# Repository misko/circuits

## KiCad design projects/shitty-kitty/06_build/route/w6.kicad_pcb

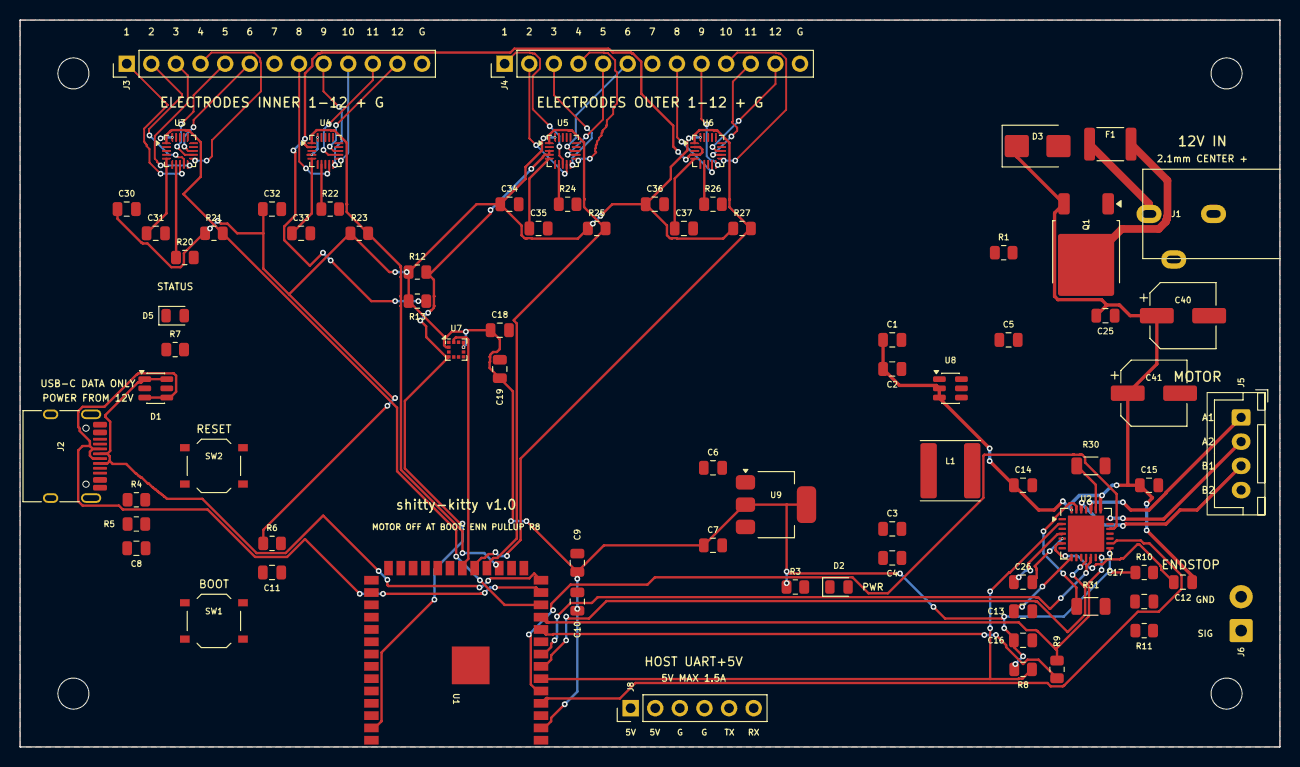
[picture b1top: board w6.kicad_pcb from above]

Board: 4 copper layers, 130.0 x 75.0 mm, 82 parts (0 on the bottom side), 79 nets.

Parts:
C1, C2: 4.7u buck in; C_0805_2012Metric
C3, C4: 22u buck out; C_0805_2012Metric
C5: 100n BST; C_0805_2012Metric
C6: 4.7u LDO in; C_0805_2012Metric
C7: 22u LDO out; C_0805_2012Metric
C8: 100n VBUS; C_0805_2012Metric
C9: 22u MCU 3V3; C_0805_2012Metric
C10: 100n MCU 3V3; C_0805_2012Metric
C11: 1u EN; C_0805_2012Metric
C12: 100n VCP; C_0805_2012Metric
C13: 4.7u 5VOUT; C_0805_2012Metric
C14, C15: 100n VS; C_0805_2012Metric
C16: 100n VCC_IO; C_0805_2012Metric
C17: 100n endstop; C_0805_2012Metric
C18: 100n accel; C_0805_2012Metric
C19: 22u accel; C_0805_2012Metric
C25: 100n 12V; C_0805_2012Metric
C26: 22n CP fly; C_0805_2012Metric
C30, C32, C34, C36: 100n MPR VDD; C_0805_2012Metric
C31, C33, C35, C37: 100n VREG; C_0805_2012Metric
C40: 100u 12V bulk; CP_Elec_6.3x7.7
C41: 100u VS bulk; CP_Elec_6.3x7.7
D1: USBLC6-2SC6; SOT-23-6
D2: green PWR; LED_0805_2012Metric
D3: SMBJ16A; D_SMB
D5: green STATUS; LED_0805_2012Metric
F1: 2A polyfuse 16V; Fuse_1812_4532Metric
H1, H2, H3, H4: MountingHole_3.2mm_M3
J1: DC-005C-20A 12V; DCJack_DC005_Horizontal
J2: TYPE-C-31-M-12; USB_C_Receptacle_HRO_TYPE-C-31-M-12
J3: ELECTRODES INNER; PinHeader_1x13_P2.54mm_Vertical
J4: ELECTRODES OUTER; PinHeader_1x13_P2.54mm_Vertical
J5: MOTOR NEMA17; JST_XH_B4B-XH-A_1x04_P2.50mm_Vertical
J6: ENDSTOP TERM; TerminalBlock_3.5-2P_NoSilk
J8: HOST 1x6; PinHeader_1x06_P2.54mm_Vertical
L1: 10uH SWPA6045S; L_Sunlord_SWPA6045S
Q1: AOD4185 revpol; TO-252-2
R1: 100k gate pd; R_0805_2012Metric
R3: 1k LED; R_0805_2012Metric
R4: 5.1k CC1; R_0805_2012Metric
R5: 5.1k CC2; R_0805_2012Metric
R6: 10k EN; R_0805_2012Metric
R7: 1k status LED; R_0805_2012Metric
R8: 10k ENN pu; R_0805_2012Metric
R9: 1k TMC UART; R_0805_2012Metric
R10: 10k endstop pu; R_0805_2012Metric
R11: 1k endstop ser; R_0805_2012Metric
R12: 4.7k SDA pu; R_0805_2012Metric
R13: 4.7k SCL pu; R_0805_2012Metric
R20, R22, R24, R26: 75k REXT; R_0805_2012Metric
R21, R23, R25, R27: 10k IRQ pu; R_0805_2012Metric
R30: 0.15R sense A; R_1206_3216Metric
R31: 0.15R sense B; R_1206_3216Metric
SW1: TS-1187A BOOT; SW_Push_1P1T_XKB_TS-1187A
SW2: TS-1187A RESET; SW_Push_1P1T_XKB_TS-1187A
U1: ESP32-S3-WROOM-1-N8R2; ESP32-S3-WROOM-1
U2: TMC2209-LA-T; QFN-28-1EP_5x5mm_P0.5mm_EP3.75x3.75mm
U3: MPR121QR2 0x5A; UQFN-20_3x3mm_P0.4mm
U4: MPR121QR2 0x5B; UQFN-20_3x3mm_P0.4mm
U5: MPR121QR2 0x5C; UQFN-20_3x3mm_P0.4mm
U6: MPR121QR2 0x5D; UQFN-20_3x3mm_P0.4mm
U7: LIS2DH12TR; LGA-12_2x2mm_P0.5mm
U8: AP63205WU-7; TSOT-23-6
U9: AMS1117-3.3; SOT-223-3_TabPin2

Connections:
3V3: C7.1, C9.1, C10.1, C16.1, C18.1, C19.1, C30.1, C32.1, C34.1, C36.1, R3.1, R6.1, R8.1, R10.1, R12.1, R13.1, R21.1, R23.1, R25.1, R27.1, U1.2, U2.15, U3.20, U4.4, U4.20, U5.20, U6.20, U7.2, U7.9, U7.10, U9.2
5V: C3.1, C4.1, C6.1, J8.1, J8.2, L1.2, U8.1, U9.3
ACC_INT: U1.20, U7.12
BOOT: SW1.1, U1.27
BRA: R30.1, U2.23
BRB: R31.1, U2.27
BST: C5.1, U8.6
CC1: J2.A5, R4.1
CC2: J2.B5, R5.1
CPI: C26.2, U2.5
CPO: C26.1, U2.4
DIAG: U1.7, U2.11
DIR: U1.5, U2.19
EN: C11.1, R6.2, SW2.1, U1.3
ENDSTOP_G: R11.2, U1.9
ENDSTOP_N: C17.1, J6.1, R10.2, R11.1
ENN: R8.2, U1.6, U2.2
GATE_Q1: Q1.1, R1.1
GND: C1.2, C2.2, C3.2, C4.2, C6.2, C7.2, C8.2, C9.2, C10.2, C11.2, C13.2, C14.2, C15.2, C16.2, C17.2, C18.2, C19.2, C25.2, C30.2, C31.2, C32.2, C33.2, C34.2, C35.2, C36.2, C37.2, C40.2, C41.2, D1.2, D2.1, D3.2, D5.1, J1.2, J1.3, J2.A1, J2.A12, J2.B1, J2.B12, J2.SH, J3.13, J4.13, J6.2, J8.3, J8.4, R1.2, R4.2, R5.2, R20.2, R22.2, R24.2, R26.2, R30.2, R31.2, SW1.2, SW2.2, U1.1, U1.40, U1.41, U2.3, U2.7, U2.9, U2.10, U2.13, U2.18, U2.29, U3.4, U3.6, U4.6, U5.6, U6.6, U7.3, U7.5, U7.6, U7.7, U7.8, U8.4, U9.1
HOST_RX: J8.6, U1.36
HOST_TX: J8.5, U1.37
INDEX: U1.8, U2.12
INNER1: J3.1, U3.8
INNER2: J3.2, U3.9
INNER3: J3.3, U3.10
INNER4: J3.4, U3.11
INNER5: J3.5, U3.12
INNER6: J3.6, U3.13
INNER7: J3.7, U4.8
INNER8: J3.8, U4.9
INNER9: J3.9, U4.10
INNER10: J3.10, U4.11
INNER11: J3.11, U4.12
INNER12: J3.12, U4.13
LED_A: D2.2, R3.2
LED_SA: D5.2, R7.2
LED_ST: R7.1, U1.21
MOT_A1: J5.1, U2.24
MOT_A2: J5.2, U2.21
MOT_B1: J5.3, U2.26
MOT_B2: J5.4, U2.1
MPR_IRQ1: R21.2, U1.12, U3.1
MPR_IRQ2: R23.2, U1.17, U4.1
MPR_IRQ3: R25.2, U1.18, U5.1
MPR_IRQ4: R27.2, U1.19, U6.1
OUTER1: J4.1, U5.8
OUTER2: J4.2, U5.9
OUTER3: J4.3, U5.10
OUTER4: J4.4, U5.11
OUTER5: J4.5, U5.12
OUTER6: J4.6, U5.13
OUTER7: J4.7, U6.8
OUTER8: J4.8, U6.9
OUTER9: J4.9, U6.10
OUTER10: J4.10, U6.11
OUTER11: J4.11, U6.12
OUTER12: J4.12, U6.13
REXT_U3: R20.1, U3.7
REXT_U4: R22.1, U4.7
REXT_U5: R24.1, U5.7
REXT_U6: R26.1, U6.7
SCL: R13.2, U1.38, U3.2, U4.2, U5.2, U6.2, U6.4, U7.1
SDA: R12.2, U1.39, U3.3, U4.3, U5.3, U5.4, U6.3, U7.4
STEP: U1.4, U2.16
SW_BUCK: C5.2, L1.1, U8.5
TMC_TX: R9.1, U1.10
TMC_UART: R9.2, U1.11, U2.14
USB_DM: D1.3, D1.4, J2.A7, J2.B7, U1.13
USB_DP: D1.1, D1.6, J2.A6, J2.B6, U1.14
USB_VBUS: C8.1, D1.5, J2.A4, J2.A9, J2.B4, J2.B9
V5OUT: C13.1, U2.8
VCP: C12.1, U2.6
VIN_12V: C1.1, C2.1, C12.2, C14.1, C15.1, C25.1, C40.1, C41.1, D3.1, Q1.3, U2.22, U2.28, U8.2, U8.3
VIN_F: F1.2, Q1.2
VIN_RAW: F1.1, J1.1
VREG_U3: C31.1, U3.5
VREG_U4: C33.1, U4.5
VREG_U5: C35.1, U5.5
VREG_U6: C37.1, U6.5

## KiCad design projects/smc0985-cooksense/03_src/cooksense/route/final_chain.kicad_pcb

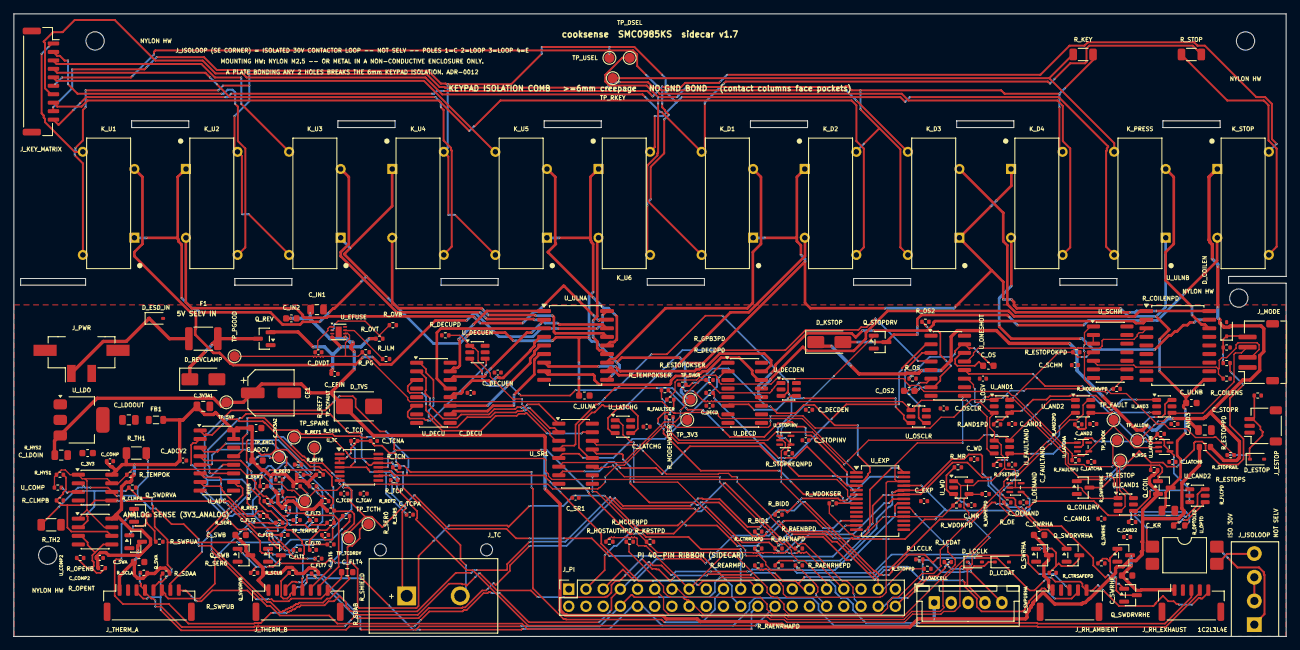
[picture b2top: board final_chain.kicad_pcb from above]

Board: 4 copper layers, 188.0 x 92.0 mm, 243 parts (0 on the bottom side), 166 nets.

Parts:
CE1: 220uF; CP_Elec_6.3x7.7
C_3V3, C_3V3A2: 100nF; C_0603_1608Metric
C_3V3A1: 10uF; C_0805_2012Metric
C_ADCV: 1uF; C_0603_1608Metric
C_ADCV2: 100nF; C_0402_1005Metric
C_AND1, C_AND2, C_AND3: 100nF; C_0402_1005Metric
C_CAND1, C_CAND2: 100nF; C_0402_1005Metric
C_COMP, C_COMP2: 100nF; C_0402_1005Metric
C_DECD: 100nF; C_0402_1005Metric
C_DECDEN: 100nF; C_0402_1005Metric
C_DECU: 100nF; C_0402_1005Metric
C_DECUEN: 100nF; C_0402_1005Metric
C_DVDT: 1nF; C_0402_1005Metric
C_EFIN: 100nF; C_0402_1005Metric
C_EXP: 100nF; C_0402_1005Metric
C_FAULTAND: 100nF; C_0402_1005Metric
C_FLT0, C_FLT1, C_FLT2, C_FLT3, C_FLT4, C_FLT5, C_FLT6, C_FLT7: 100nF; C_0402_1005Metric
C_IN1: 10uF; C_0805_2012Metric
C_IN2: 100nF; C_0603_1608Metric
C_KR: 10uF; C_0805_2012Metric
C_LATCHA: 100nF; C_0402_1005Metric
C_LATCHB: 100nF; C_0402_1005Metric
C_LATCHG: 100nF; C_0402_1005Metric
C_LDOIN: 10uF; C_0805_2012Metric
C_LDOOUT: 22uF; C_0805_2012Metric
C_MR: 100nF; C_0402_1005Metric
C_OENAND: 100nF; C_0402_1005Metric
C_OS, C_OS2: 1uF; C_0603_1608Metric
C_OSCLR: 100nF; C_0402_1005Metric
C_OSV: 100nF; C_0402_1005Metric
C_SCHM: 100nF; C_0402_1005Metric
C_SR1: 100nF; C_0402_1005Metric
C_STOPINV: 100nF; C_0402_1005Metric
C_STOPR: 10uF; C_0805_2012Metric
C_SWA: 1uF; C_0603_1608Metric
C_SWB: 1uF; C_0603_1608Metric
C_SWRHA: 1uF; C_0603_1608Metric
C_SWRHE: 1uF; C_0603_1608Metric
C_TCAV: 100nF; C_0402_1005Metric
C_TCD: 100nF; C_0402_1005Metric
C_TCDV: 100nF; C_0402_1005Metric
C_TCNA: 10nF; C_0402_1005Metric
C_TCPA: 10nF; C_0402_1005Metric
C_ULNA: 100nF; C_0603_1608Metric
C_ULNB: 100nF; C_0603_1608Metric
C_WD: 100nF; C_0402_1005Metric
D_COILEN: C5158048; D_SOD-323
D_ESD_IN: C5158048; D_SOD-323
D_ESTOP: C5158048; D_SOD-323
D_KSTOP: C8678; D_SMA
D_LCCLK: C5158048; D_SOD-323
D_LCDAT: C5158048; D_SOD-323
D_REVCLAMP: C8678; D_SMA
D_TVS: C113974; D_SMB
F1: C89650; Fuse_1812_4532Metric
FB1: C1017; L_0805_2012Metric
H1, H2, H3, H4: MountingHole_2.7mm_M2.5_ISO14580
J_ESTOP: C160403; JST_SH_SM03B-SRSS-TB_1x03-1MP_P1.00mm_Horizontal
J_ISOLOOP: KF350-3.5-4P; TerminalBlock_KF350_4P
J_KEY_MATRIX: C2683602; JST_GH_SM10B-GHS-TB_1x10-1MP_P1.25mm_Horizontal
J_LOADCELL: C157991; JST_XH_B5B-XH-A_1x05_P2.50mm_Vertical
J_MODE: C485354; JST_ZH_S4B-ZR-SM4A-TF_1x04-1MP_P1.50mm_Horizontal
J_PI: C35165; PinSocket_2x20_P2.54mm_Vertical
J_PWR: C587657; Molex_Micro-Fit_3.0_43650-0224_1x02-1MP_P3.00mm_Vertical
J_RH_AMBIENT: C189896; JST_GH_SM05B-GHS-TB_1x05-1MP_P1.25mm_Horizontal
J_RH_EXHAUST: C189896; JST_GH_SM05B-GHS-TB_1x05-1MP_P1.25mm_Horizontal
J_TC: PCC-SMP-K; Omega_PCC-SMP-K_TypeK_PCpin
J_THERM_A: C265111; JST_GH_SM08B-GHS-TB_1x08-1MP_P1.25mm_Horizontal
J_THERM_B: C265111; JST_GH_SM08B-GHS-TB_1x08-1MP_P1.25mm_Horizontal
K_D1, K_D2, K_D3, K_D4: DIP05-1A72-13L; Relay_StandexDIP_1A_pinout13
K_PRESS: DIP05-1A72-13L; Relay_StandexDIP_1A_pinout13
K_STOP: DIP05-1A72-13L; Relay_StandexDIP_1A_pinout13
K_U1, K_U2, K_U3, K_U4, K_U5, K_U6: DIP05-1A72-13L; Relay_StandexDIP_1A_pinout13
Q_COIL: C15127; SOT-23
Q_COILDRV: C8545; SOT-23
Q_REV: C15127; SOT-23
Q_STOPDRV: C8545; SOT-23
Q_SWA: C15127; SOT-23
Q_SWB: C15127; SOT-23
Q_SWDRVA: C8545; SOT-23
Q_SWDRVB: C8545; SOT-23
Q_SWDRVRHA: C8545; SOT-23
Q_SWDRVRHE: C8545; SOT-23
Q_SWRHA: C15127; SOT-23
Q_SWRHE: C15127; SOT-23
R_AND1PD, R_AND2PD: 100kΩ; R_0402_1005Metric
R_BID0, R_BID1: 10kΩ; R_0402_1005Metric
R_CLMPA: 22kΩ; R_0402_1005Metric
R_CLMPB: 22kΩ; R_0402_1005Metric
R_COILENPD: 680Ω; R_0402_1005Metric
R_COILENS: 680Ω; R_0402_1005Metric
R_CTRREQPD: 100kΩ; R_0402_1005Metric
R_CTRSAFEPD: 100kΩ; R_0402_1005Metric
R_DECDPD: 100kΩ; R_0402_1005Metric
R_DECUPD: 100kΩ; R_0402_1005Metric
R_ESTOPOKPD: 100kΩ; R_0402_1005Metric
R_ESTOPOKSER: 10kΩ; R_0402_1005Metric
R_ESTOPPD: 470Ω; R_0402_1005Metric
R_ESTOPS: 680Ω; R_0402_1005Metric
R_FAULTPU: 100kΩ; R_0402_1005Metric
R_FAULTSER: 10kΩ; R_0402_1005Metric
R_FLCPD: 100kΩ; R_0402_1005Metric
R_FSETNPD: 100kΩ; R_0402_1005Metric
R_GPB3PD: 10kΩ; R_0402_1005Metric
R_HOSTAUTHPD: 100kΩ; R_0402_1005Metric
R_HSG: 100kΩ; R_0402_1005Metric
R_HYS1, R_HYS2: 1MΩ; R_0402_1005Metric
R_ILM: 1.2kΩ; R_0402_1005Metric
R_KEY: 0Ω; R_1206_3216Metric
R_KRSTPD: 100kΩ; R_0402_1005Metric
R_LCCLK: 33Ω; R_0402_1005Metric
R_LCDAT: 33Ω; R_0402_1005Metric
R_MCUENPD: 100kΩ; R_0402_1005Metric
R_MODEHWPD: 100kΩ; R_0402_1005Metric
R_MODEHWSER: 10kΩ; R_0402_1005Metric
R_MODEPD: 10kΩ; R_0402_1005Metric
R_MR: 100kΩ; R_0402_1005Metric
R_OE: 10kΩ; R_0402_1005Metric
R_OPENB: 100kΩ; R_0402_1005Metric
R_OPENT: 62kΩ; R_0402_1005Metric
R_OPTOLED: 330Ω; R_0603_1608Metric
R_OS: 510kΩ; R_0402_1005Metric
R_OS2: 10kΩ; R_0402_1005Metric
R_OVB: 26.1kΩ; R_0402_1005Metric
R_OVT: 100kΩ; R_0402_1005Metric
R_PG: 100kΩ; R_0402_1005Metric
R_RAENAPD: 100kΩ; R_0402_1005Metric
R_RAENBPD: 100kΩ; R_0402_1005Metric
R_RAENRHAPD: 100kΩ; R_0402_1005Metric
R_RAENRHEPD: 100kΩ; R_0402_1005Metric
R_REARMPU: 100kΩ; R_0402_1005Metric
R_REF0, R_REF1, R_REF2, R_REF3, R_REF4, R_REF5, R_REF6, R_REF7: 10kΩ; R_0402_1005Metric
R_SCLA: 2.2kΩ; R_0402_1005Metric
R_SCLB: 2.2kΩ; R_0402_1005Metric
R_SDAA: 2.2kΩ; R_0402_1005Metric
R_SDAB: 2.2kΩ; R_0402_1005Metric
R_SER0, R_SER1, R_SER2, R_SER3, R_SER4, R_SER5, R_SER6, R_SER7: 1kΩ; R_0402_1005Metric
R_SHIELD: 0Ω; R_0603_1608Metric
R_STOP: 0Ω; R_1206_3216Metric
R_STOPPD: 100kΩ; R_0402_1005Metric
R_STOPRAIL: 0Ω; R_0603_1608Metric
R_STOPREQNPD: 100kΩ; R_0402_1005Metric
R_SWPUA: 100kΩ; R_0402_1005Metric
R_SWPUB: 100kΩ; R_0402_1005Metric
R_SWPURHA: 100kΩ; R_0402_1005Metric
R_SWPURHE: 100kΩ; R_0402_1005Metric
R_TCN: 100Ω; R_0402_1005Metric
R_TCP: 100Ω; R_0402_1005Metric
R_TEMPOK: 10kΩ; R_0402_1005Metric
R_TEMPOKSER: 10kΩ; R_0402_1005Metric
R_TH1: 68kΩ; R_1206_3216Metric
R_TH2: 10kΩ; R_1206_3216Metric
R_WDOKPD: 100kΩ; R_0402_1005Metric
R_WDOKSER: 10kΩ; R_0402_1005Metric
R_WDPETPD: 1kΩ; R_0402_1005Metric
TP_3V3, TP_5VKR, TP_5VP: TP; TestPoint_Pad_D1.5mm
TP_ALLOW: TP; TestPoint_Pad_D1.5mm
TP_DSEL: TP; TestPoint_Pad_D1.5mm
TP_ENCL: TP; TestPoint_Pad_D1.5mm
TP_ESTOP: TP; TestPoint_Pad_D1.5mm
TP_FAULT: TP; TestPoint_Pad_D1.5mm
TP_PGOOD: TP; TestPoint_Pad_D1.5mm
TP_RKEY: TP; TestPoint_Pad_D1.5mm
TP_SPARE: TP; TestPoint_Pad_D1.5mm
TP_TCDRDY: TP; TestPoint_Pad_D1.5mm
TP_TCFAULT: TP; TestPoint_Pad_D1.5mm
TP_TCTH: TP; TestPoint_Pad_D1.5mm
TP_TEMPOK: TP; TestPoint_Pad_D1.5mm
TP_USEL: TP; TestPoint_Pad_D1.5mm
TP_WDOK: TP; TestPoint_Pad_D1.5mm
U_ADC: C16939; SOIC-16_3.9x9.9mm_P1.27mm
U_AND1, U_AND2, U_AND3: C22046; SOT-23-6
U_CAND1, U_CAND2: C22046; SOT-23-6
U_COMP, U_COMP2: C7984; SOIC-8_3.9x4.9mm_P1.27mm
U_DECD: C5620; SOIC-16_3.9x9.9mm_P1.27mm
U_DECDEN: C22046; SOT-23-6
U_DECU: C5620; SOIC-16_3.9x9.9mm_P1.27mm
U_DECUEN: C22046; SOT-23-6
U_EFUSE: C2653844; Texas_DSG0008A_WSON-8-1EP_2x2mm_P0.5mm_EP0.9x1.6mm
U_EXP: C558584; SSOP-28_5.3x10.2mm_P0.65mm
U_FAULTAND: C22046; SOT-23-6
U_LATCHA: C8185; SOT-353_SC-70-5
U_LATCHB: C8185; SOT-353_SC-70-5
U_LATCHG: C22046; SOT-23-6
U_LDO: C6186; SOT-223
U_OENAND: C8185; SOT-353_SC-70-5
U_ONESHOT: C133954; SOIC-16_3.9x9.9mm_P1.27mm
U_OPTO: C125121; SMDIP-4_W9.53mm
U_OSCLR: C22046; SOT-23-6
U_SCHM: C6820; SOIC-14_3.9x8.7mm_P1.27mm
U_SR1: C10092; SOIC-16_3.9x9.9mm_P1.27mm
U_STOPINV: C8185; SOT-353_SC-70-5
U_TC: C2653162; TSSOP-14_4.4x5mm_P0.65mm
U_ULNA: C165895; SOIC-18W_7.5x11.6mm_P1.27mm
U_ULNB: C165895; SOIC-18W_7.5x11.6mm_P1.27mm
U_WD: C7719; SOT-23-5

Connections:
3V3: C_3V3.1, C_AND1.1, C_AND2.1, C_AND3.1, C_CAND1.1, C_CAND2.1, C_DECD.1, C_DECDEN.1, C_DECU.1, C_DECUEN.1, C_EXP.1, C_FAULTAND.1, C_LATCHA.1, C_LATCHB.1, C_LATCHG.1, C_LDOOUT.1, C_OENAND.1, C_OSCLR.1, C_OSV.1, C_SCHM.1, C_SR1.1, C_STOPINV.1, C_TCAV.1, C_TCDV.1, C_WD.1, FB1.1, J_ESTOP.2, J_LOADCELL.2, J_MODE.1, Q_SWA.2, Q_SWB.2, Q_SWRHA.2, Q_SWRHE.2, R_BID1.2, R_FAULTPU.2, R_MR.2, R_OE.2, R_OS.2, R_OS2.2, R_PG.2, R_REARMPU.2, R_SWPUA.2, R_SWPUB.2, R_SWPURHA.2, R_SWPURHE.2, TP_3V3.1, U_AND1.5, U_AND2.5, U_AND3.5, U_CAND1.5, U_CAND2.5, U_DECD.16, U_DECDEN.5, U_DECDEN.6, U_DECU.16, U_DECUEN.5, U_DECUEN.6, U_EXP.9, U_FAULTAND.5, U_LATCHA.5, U_LATCHB.5, U_LATCHG.5, U_LATCHG.6, U_LDO.2, U_LDO.4, U_OENAND.5, U_ONESHOT.10, U_ONESHOT.16, U_OSCLR.5, U_OSCLR.6, U_SCHM.14, U_SR1.16, U_STOPINV.5, U_TC.5, U_TC.8, U_WD.5
3V3_ANALOG: C_3V3A1.1, C_3V3A2.1, C_ADCV.1, C_ADCV2.1, C_COMP.1, C_COMP2.1, FB1.2, R_OPENT.1, R_REF0.1, R_REF1.1, R_REF2.1, R_REF3.1, R_REF4.1, R_REF5.1, R_REF6.1, R_REF7.1, R_TEMPOK.2, R_TH1.1, U_ADC.15, U_ADC.16, U_COMP.8, U_COMP2.8
3V3_SW_A: C_SWA.1, J_THERM_A.1, Q_SWA.3, R_SCLA.2, R_SDAA.2
3V3_SW_B: C_SWB.1, J_THERM_B.1, Q_SWB.3, R_SCLB.2, R_SDAB.2
3V3_SW_RHA: C_SWRHA.1, J_RH_AMBIENT.1, Q_SWRHA.3
3V3_SW_RHE: C_SWRHE.1, J_RH_EXHAUST.1, Q_SWRHE.3
5V_FUSED: D_REVCLAMP.1, F1.2, Q_REV.3
5V_IN: D_ESD_IN.1, F1.1, J_PWR.1
5V_KEY_RELAY: C_KR.1, C_ULNA.1, C_ULNB.1, K_D1.1, K_D2.1, K_D3.1, K_D4.1, K_PRESS.1, K_U1.1, K_U2.1, K_U3.1, K_U4.1, K_U5.1, K_U6.1, Q_COIL.3, TP_5VKR.1, U_ULNA.10, U_ULNB.10
5V_PROTECTED: CE1.1, C_IN1.1, C_IN2.1, C_LDOIN.1, D_TVS.1, J_LOADCELL.1, Q_COIL.2, R_HSG.2, R_STOPRAIL.1, TP_5VP.1, U_EFUSE.5, U_LDO.3
5V_RPP: C_EFIN.1, Q_REV.2, R_OVT.1, U_EFUSE.3, U_EFUSE.4
5V_STOP: C_STOPR.1, D_KSTOP.1, K_STOP.1, R_STOPRAIL.2
ADC_CH0: C_FLT0.1, R_SER0.2, U_ADC.1
ADC_CH1: C_FLT1.1, R_SER1.2, U_ADC.2
ADC_CH2: C_FLT2.1, R_SER2.2, U_ADC.3
ADC_CH3: C_FLT3.1, R_SER3.2, U_ADC.4
ADC_CH4: C_FLT4.1, R_SER4.2, U_ADC.5
ADC_CH5: C_FLT5.1, R_SER5.2, U_ADC.6
ADC_CH6: C_FLT6.1, R_SER6.2, U_ADC.7
ADC_CH7: C_FLT7.1, R_SER7.2, U_ADC.8
ADC_CS_N: J_PI.24, U_ADC.10
AND1: R_AND1PD.1, U_AND1.4, U_AND3.1
AND2: R_AND2PD.1, U_AND2.4, U_AND3.3
BOARD_ID0: R_BID0.1, U_EXP.27
BOARD_ID1: R_BID1.1, U_EXP.28
COIL_D1_N: K_D1.2, U_ULNA.12
COIL_D2_N: K_D2.2, U_ULNA.11
COIL_D3_N: K_D3.2, U_ULNB.18
COIL_D4_N: K_D4.2, U_ULNB.17
COIL_EN: Q_COILDRV.1, R_COILENS.2
COIL_EN_IN: D_COILEN.1, J_MODE.4, R_COILENPD.1, R_COILENS.1
COIL_PRESS_N: K_PRESS.2, U_ULNB.16
COIL_STOP_N: D_KSTOP.2, K_STOP.2, Q_STOPDRV.3
COIL_U1_N: K_U1.2, U_ULNA.18
COIL_U2_N: K_U2.2, U_ULNA.17
COIL_U3_N: K_U3.2, U_ULNA.16
COIL_U4_N: K_U4.2, U_ULNA.15
COIL_U5_N: K_U5.2, U_ULNA.14
COIL_U6_N: K_U6.2, U_ULNA.13
CONTACTOR_C: J_ISOLOOP.1, U_OPTO.4
CONTACTOR_DRV: R_OPTOLED.1, U_CAND2.4
CONTACTOR_E: J_ISOLOOP.4, U_OPTO.3
CONTACTOR_LOOP: J_ISOLOOP.2, J_ISOLOOP.3
CONTACTOR_REQ: R_CTRREQPD.1, U_CAND2.6, U_EXP.25
CTR_SAFE: R_CTRSAFEPD.1, U_CAND1.4, U_CAND2.1
DECD_A: U_DECD.1, U_SR1.4
DECD_B: U_DECD.2, U_SR1.5
DECD_G1: U_DECD.6, U_DECDEN.4
DECD_G1_RAW: R_DECDPD.1, U_DECDEN.1, U_SR1.6
DECU_A: U_DECU.1, U_SR1.15
DECU_B: U_DECU.2, U_SR1.1
DECU_C: U_DECU.3, U_SR1.2
DECU_G1: U_DECU.6, U_DECUEN.4
DECU_G1_RAW: R_DECUPD.1, U_DECUEN.1, U_SR1.3
D_SEL_BUS: K_D1.4, K_D2.4, K_D3.4, K_D4.4, R_KEY.2, TP_DSEL.1
EFUSE_FLT_N: R_PG.1, TP_PGOOD.1, U_EFUSE.6, U_EXP.1
EF_DVDT: C_DVDT.1, U_EFUSE.1
EF_ILM: R_ILM.1, U_EFUSE.7
EF_OVLO: R_OVB.1, R_OVT.2, U_EFUSE.2
ESTOP_NI: U_SCHM.2, U_SCHM.3
ESTOP_OK: R_ESTOPOKPD.1, R_ESTOPOKSER.1, TP_ESTOP.1, U_AND1.6, U_CAND1.3, U_FAULTAND.3, U_OSCLR.1, U_SCHM.4
ESTOP_OK_EXP: R_ESTOPOKSER.2, U_EXP.3
ESTOP_RAW: R_ESTOPS.2, U_SCHM.1
ESTOP_RAW_IN: D_ESTOP.1, J_ESTOP.3, R_ESTOPPD.1, R_ESTOPS.1
FAULT: R_FAULTPU.1, R_FAULTSER.1, TP_FAULT.1, U_LATCHA.4, U_LATCHB.2
FAULT_EXP: R_FAULTSER.2, U_EXP.6
FAULT_LATCH_CLEAR: R_FLCPD.1, U_AND3.6, U_CAND2.3, U_LATCHA.2, U_LATCHB.4
FAULT_SET_N: R_FSETNPD.1, U_FAULTAND.4, U_LATCHA.1
GND: CE1.2, C_3V3.2, C_3V3A1.2, C_3V3A2.2, C_ADCV.2, C_ADCV2.2, C_AND1.2, C_AND2.2, C_AND3.2, C_CAND1.2, C_CAND2.2, C_COMP.2, C_COMP2.2, C_DECD.2, C_DECDEN.2, C_DECU.2, C_DECUEN.2, C_DVDT.2, C_EFIN.2, C_EXP.2, C_FAULTAND.2, C_FLT0.2, C_FLT1.2, C_FLT2.2, C_FLT3.2, C_FLT4.2, C_FLT5.2, C_FLT6.2, C_FLT7.2, C_IN1.2, C_IN2.2, C_KR.2, C_LATCHA.2, C_LATCHB.2, C_LATCHG.2, C_LDOIN.2, C_LDOOUT.2, C_MR.2, C_OENAND.2, C_OSCLR.2, C_OSV.2, C_SCHM.2, C_SR1.2, C_STOPINV.2, C_STOPR.2, C_SWA.2, C_SWB.2, C_SWRHA.2, C_SWRHE.2, C_TCAV.2, C_TCDV.2, C_TCNA.2, C_TCPA.2, C_ULNA.2, C_ULNB.2, C_WD.2, D_COILEN.2, D_ESD_IN.2, D_ESTOP.2, D_LCCLK.2, D_LCDAT.2, D_REVCLAMP.2, D_TVS.2, J_ESTOP.1, J_ESTOP.MP, J_LOADCELL.3, J_MODE.MP, J_PI.6, J_PI.9, J_PI.14, J_PI.20, J_PI.25, J_PI.30, J_PI.34, J_PI.39, J_PWR.2, J_PWR.MP, J_RH_AMBIENT.2, J_RH_AMBIENT.MP, J_RH_EXHAUST.2, J_RH_EXHAUST.MP, J_THERM_A.2, J_THERM_A.MP, J_THERM_B.2, J_THERM_B.MP, Q_COILDRV.2, Q_REV.1, Q_STOPDRV.2, Q_SWDRVA.2, Q_SWDRVB.2, Q_SWDRVRHA.2, Q_SWDRVRHE.2, R_AND1PD.2, R_AND2PD.2, R_BID0.2, R_CLMPA.2, R_CLMPB.2, R_COILENPD.2, R_CTRREQPD.2, R_CTRSAFEPD.2, R_DECDPD.2, R_DECUPD.2, R_ESTOPOKPD.2, R_ESTOPPD.2, R_FLCPD.2, R_FSETNPD.2, R_GPB3PD.1, R_HOSTAUTHPD.2, R_ILM.2, R_KRSTPD.2, R_MCUENPD.2, R_MODEHWPD.2, R_MODEPD.2, R_OPENB.2, R_OVB.2, R_RAENAPD.2, R_RAENBPD.2, R_RAENRHAPD.2, R_RAENRHEPD.2, R_SHIELD.2, R_STOPPD.2, R_STOPREQNPD.2, R_TH2.2, R_WDOKPD.2, R_WDPETPD.2, U_ADC.9, U_ADC.14, U_AND1.2, U_AND2.2, U_AND3.2, U_CAND1.2, U_CAND2.2, U_COMP.4, U_COMP2.4, U_DECD.3, U_DECD.4, U_DECD.5, U_DECD.8, U_DECDEN.2, U_DECU.4, U_DECU.5, U_DECU.8, U_DECUEN.2, U_EFUSE.8, U_EFUSE.9, U_EXP.10, U_EXP.15, U_EXP.16, U_EXP.17, U_FAULTAND.2, U_LATCHA.3, U_LATCHB.3, U_LATCHG.2, U_LDO.1, U_OENAND.3, U_ONESHOT.1, U_ONESHOT.8, U_OPTO.2, U_OSCLR.2, U_SCHM.7, U_SCHM.11, U_SCHM.13, U_SR1.8, U_STOPINV.3, U_TC.1, U_TC.14, U_ULNA.9, U_ULNB.4, U_ULNB.9, U_WD.2
GPB3_SPARE: R_GPB3PD.2, U_EXP.4
HOST_AUTH: J_PI.15, R_HOSTAUTHPD.1, U_AND2.6
HS_GATE_COIL: Q_COIL.1, Q_COILDRV.3, R_HSG.1
I2C_SCL: J_PI.5, U_EXP.12
I2C_SDA: J_PI.3, U_EXP.13
INT_ALERT: J_PI.13, U_EXP.20
KEY_CLOCK: J_PI.31, U_SR1.11
KEY_DATA: J_PI.36, U_SR1.14
KEY_LATCH: J_PI.32, U_LATCHG.1
KEY_LATCH_G: U_LATCHG.4, U_SR1.12
KEY_RELAY_ALLOWED: J_MODE.3, TP_ALLOW.1, U_AND3.4
KEY_RESET_N: J_PI.33, R_KRSTPD.1, U_SR1.10
KP_D1: J_KEY_MATRIX.7, K_D1.3, R_STOP.2
KP_D2: J_KEY_MATRIX.8, K_D2.3
KP_D3: J_KEY_MATRIX.9, K_D3.3
KP_D4: J_KEY_MATRIX.10, K_D4.3
KP_U1: J_KEY_MATRIX.1, K_U1.3
KP_U2: J_KEY_MATRIX.2, K_U2.3
KP_U3: J_KEY_MATRIX.3, K_U3.3
KP_U4: J_KEY_MATRIX.4, K_U4.3
KP_U5: J_KEY_MATRIX.5, K_U5.3
KP_U6: J_KEY_MATRIX.6, K_STOP.4, K_U6.3
LC_CLK: D_LCCLK.1, J_LOADCELL.5, R_LCCLK.1
LC_CLK_PI: J_PI.40, R_LCCLK.2
LC_DAT: D_LCDAT.1, J_LOADCELL.4, R_LCDAT.1
LC_DAT_PI: J_PI.38, R_LCDAT.2
MCU_RELAY_ENABLE: J_PI.16, R_MCUENPD.1, U_AND2.3, U_OENAND.1
MODE_AUTO_HW: R_MODEHWPD.1, R_MODEHWSER.1, U_AND1.1, U_SCHM.8
MODE_AUTO_HW_EXP: R_MODEHWSER.2, U_EXP.2
MODE_NI: U_SCHM.6, U_SCHM.9
MODE_RAW: J_MODE.2, R_MODEPD.1, U_SCHM.5
OPTO_LED_A: R_OPTOLED.2, U_OPTO.1
OS2_C: C_OS2.1, U_ONESHOT.6
OS2_RC: C_OS2.2, R_OS2.1, U_ONESHOT.7
OS_C: C_OS.1, U_ONESHOT.14
OS_CLR_N: U_ONESHOT.3, U_OSCLR.4
OS_RC: C_OS.2, R_OS.1, U_ONESHOT.15
PRESS_REQ: U_ONESHOT.2, U_SR1.7
PRESS_TIMED: U_ONESHOT.13, U_ULNB.3
PRESS_TIMED_N: U_LATCHG.3, U_ONESHOT.4
RAIL_EN_A: Q_SWDRVA.1, R_RAENAPD.1, U_EXP.21
RAIL_EN_B: Q_SWDRVB.1, R_RAENBPD.1, U_EXP.22
RAIL_EN_RHA: Q_SWDRVRHA.1, R_RAENRHAPD.1, U_EXP.23
RAIL_EN_RHE: Q_SWDRVRHE.1, R_RAENRHEPD.1, U_EXP.24
REARM_N: R_REARMPU.1, U_EXP.26, U_ONESHOT.9
REARM_PULSE_N: U_LATCHB.1, U_ONESHOT.12
RKEY_MID: K_PRESS.3, R_KEY.1, TP_RKEY.1
RSTOP_MID: K_STOP.3, R_STOP.1
SCL_A: J_PI.29, J_RH_AMBIENT.4, J_THERM_A.4, R_SCLA.1
SCL_B: J_PI.10, J_RH_EXHAUST.4, J_THERM_B.4, R_SCLB.1
SDA_A: J_PI.7, J_RH_AMBIENT.3, J_THERM_A.3, R_SDAA.1
SDA_B: J_PI.8, J_RH_EXHAUST.3, J_THERM_B.3, R_SDAB.1
SEL_D1: U_DECD.15, U_ULNA.7
SEL_D2: U_DECD.14, U_ULNA.8
SEL_D3: U_DECD.13, U_ULNB.1
SEL_D4: U_DECD.12, U_ULNB.2
SEL_U1: U_DECU.15, U_ULNA.1
SEL_U2: U_DECU.14, U_ULNA.2
SEL_U3: U_DECU.13, U_ULNA.3
SEL_U4: U_DECU.12, U_ULNA.4
SEL_U5: U_DECU.11, U_ULNA.5
SEL_U6: U_DECU.10, U_ULNA.6
SHIELD_DRAIN: J_RH_AMBIENT.5, J_RH_EXHAUST.5, J_THERM_A.8, J_THERM_B.8, R_SHIELD.1
SPI_MISO: J_PI.21, U_ADC.12, U_TC.11
SPI_MOSI: J_PI.19, U_ADC.11, U_TC.12
SPI_SCLK: J_PI.23, U_ADC.13, U_TC.10
SR_OE_N: R_OE.1, U_OENAND.4, U_SR1.13
STOP_REQ: J_PI.37, Q_STOPDRV.1, R_STOPPD.1, U_STOPINV.1, U_STOPINV.2
STOP_REQ_N: R_STOPREQNPD.1, U_DECDEN.3, U_DECUEN.3, U_OSCLR.3, U_STOPINV.4
SWG_A: Q_SWA.1, Q_SWDRVA.3, R_SWPUA.1
SWG_B: Q_SWB.1, Q_SWDRVB.3, R_SWPUB.1
SWG_RHA: Q_SWDRVRHA.3, Q_SWRHA.1, R_SWPURHA.1
SWG_RHE: Q_SWDRVRHE.3, Q_SWRHE.1, R_SWPURHE.1
TCAM_OPEN: R_OPENB.1, R_OPENT.2, U_COMP2.3, U_COMP2.5
TCAM_THRESH: R_TH1.2, R_TH2.1, TP_TCTH.1, U_COMP.2, U_COMP.6
TC_CS_N: J_PI.26, U_TC.9
TC_DRDY_N: J_PI.22, TP_TCDRDY.1, U_TC.7
TC_FAULT_N: TP_TCFAULT.1, U_EXP.7, U_TC.13
TC_NEG: C_TCD.2, C_TCNA.1, R_TCN.2, U_TC.2, U_TC.3
TC_NEG_IN: J_TC.2, R_TCN.1
TC_POS: C_TCD.1, C_TCPA.1, R_TCP.2, U_TC.4
TC_POS_IN: J_TC.1, R_TCP.1
TEMP_OK: R_HYS1.1, R_HYS2.1, R_TEMPOK.1, R_TEMPOKSER.1, TP_TEMPOK.1, U_AND2.1, U_CAND1.6, U_COMP.1, U_COMP.7, U_COMP2.1, U_COMP2.7, U_FAULTAND.6
TEMP_OK_EXP: R_TEMPOKSER.2, U_EXP.5
TH_CAM_A: J_THERM_A.5, R_CLMPA.1, R_HYS1.2, R_REF0.2, R_SER0.1, U_COMP.3, U_COMP2.2
TH_CAM_B: J_THERM_B.5, R_CLMPB.1, R_HYS2.2, R_REF3.2, R_SER3.1, U_COMP.5, U_COMP2.6
TH_ENCLOSURE: R_REF6.2, R_SER6.1, TP_ENCL.1
TH_MOUNT_A: J_THERM_A.6, R_REF1.2, R_SER1.1
TH_MOUNT_B: J_THERM_B.6, R_REF4.2, R_SER4.1
TH_PORT_A: J_THERM_A.7, R_REF2.2, R_SER2.1
TH_PORT_B: J_THERM_B.7, R_REF5.2, R_SER5.1
TH_SPARE: R_REF7.2, R_SER7.1, TP_SPARE.1
U_SEL_BUS: K_PRESS.4, K_U1.4, K_U2.4, K_U3.4, K_U4.4, K_U5.4, K_U6.4, TP_USEL.1
WD_MR_N: C_MR.1, R_MR.1, U_WD.3
WD_OK: R_WDOKPD.1, R_WDOKSER.1, TP_WDOK.1, U_AND1.3, U_CAND1.1, U_EXP.18, U_FAULTAND.1, U_OENAND.2, U_ONESHOT.11, U_WD.1
WD_OK_EXP: R_WDOKSER.2, U_EXP.8
WD_PET: J_PI.11, R_WDPETPD.1, U_WD.4

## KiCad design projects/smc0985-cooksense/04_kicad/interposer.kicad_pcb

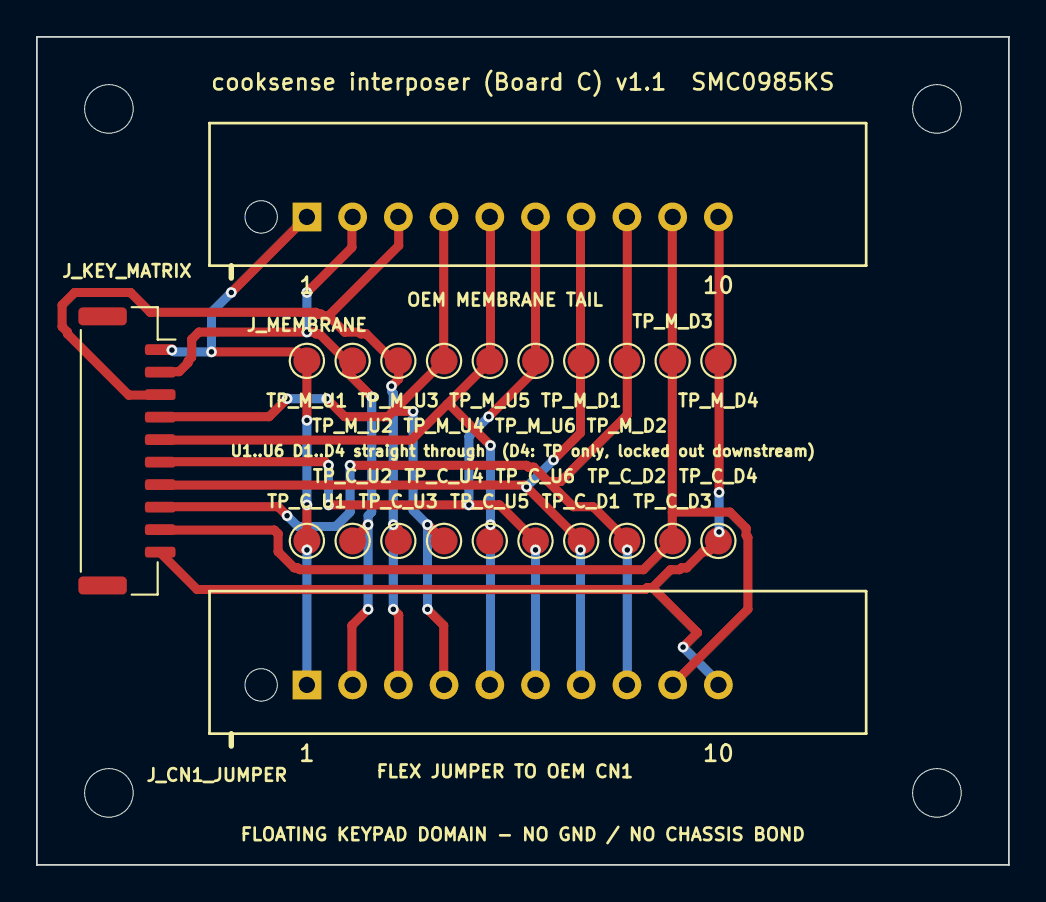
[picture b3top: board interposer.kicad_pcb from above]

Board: 2 copper layers, 54.0 x 46.0 mm, 27 parts (0 on the bottom side), 10 nets.

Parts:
H1, H2, H3, H4: MountingHole_2.7mm_M2.5_ISO14580
J_CN1_JUMPER: 10FDZ-BT; JST_10FDZ-BT_1x10_P2.54mm_Vertical_ZIF
J_KEY_MATRIX: C2683602; JST_GH_SM10B-GHS-TB_1x10-1MP_P1.25mm_Horizontal
J_MEMBRANE: 10FDZ-BT; JST_10FDZ-BT_1x10_P2.54mm_Vertical_ZIF
TP_C_D1, TP_C_D2, TP_C_D3, TP_C_D4: TP; TestPoint_Pad_D1.5mm
TP_C_U1, TP_C_U2, TP_C_U3, TP_C_U4, TP_C_U5, TP_C_U6: TP; TestPoint_Pad_D1.5mm
TP_M_D1, TP_M_D2, TP_M_D3, TP_M_D4: TP; TestPoint_Pad_D1.5mm
TP_M_U1, TP_M_U2, TP_M_U3, TP_M_U4, TP_M_U5, TP_M_U6: TP; TestPoint_Pad_D1.5mm

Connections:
KP_D1: J_CN1_JUMPER.7, J_KEY_MATRIX.7, J_MEMBRANE.7, TP_C_D1.1, TP_M_D1.1
KP_D2: J_CN1_JUMPER.8, J_KEY_MATRIX.8, J_MEMBRANE.8, TP_C_D2.1, TP_M_D2.1
KP_D3: J_CN1_JUMPER.9, J_KEY_MATRIX.9, J_MEMBRANE.9, TP_C_D3.1, TP_M_D3.1
KP_D4: J_CN1_JUMPER.10, J_KEY_MATRIX.10, J_MEMBRANE.10, TP_C_D4.1, TP_M_D4.1
KP_U1: J_CN1_JUMPER.1, J_KEY_MATRIX.1, J_MEMBRANE.1, TP_C_U1.1, TP_M_U1.1
KP_U2: J_CN1_JUMPER.2, J_KEY_MATRIX.2, J_MEMBRANE.2, TP_C_U2.1, TP_M_U2.1
KP_U3: J_CN1_JUMPER.3, J_KEY_MATRIX.3, J_MEMBRANE.3, TP_C_U3.1, TP_M_U3.1
KP_U4: J_CN1_JUMPER.4, J_KEY_MATRIX.4, J_MEMBRANE.4, TP_C_U4.1, TP_M_U4.1
KP_U5: J_CN1_JUMPER.5, J_KEY_MATRIX.5, J_MEMBRANE.5, TP_C_U5.1, TP_M_U5.1
KP_U6: J_CN1_JUMPER.6, J_KEY_MATRIX.6, J_MEMBRANE.6, TP_C_U6.1, TP_M_U6.1
